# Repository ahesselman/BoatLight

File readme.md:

# Boat light controller

Controller for a boat light which indicates port and starboard. 

## Description

BoatLight is an LED ring system designed to indicate the port (red) and starboard (green) sides of a boat. It supports eight user-selectable modes, which can be toggled using a physical button. The currently selected mode is saved to persistent storage, so it resumes automatically after a power cycle.

The device is solar-powered. It monitors the voltage from a connected solar panel to determine whether it should be active or idle. When the solar panel voltage drops below 2.35V, the device activates. When the voltage rises above 2.40V, the device enters an idle state to conserve power.

## System overview

* **Power source**: solar panel and USB input
* **Battery**: ?
* **Charging module**: TP4056 for battery charging management
* **Microcontroller**: ATTiny85 for controlling the LEDs and handling user input
* **LEDs**: 16 SK6812 addressable RGBW LEDs
* **User input**: Single push-button for mode selection
* **Power control**: P-channel MOSFET to switch LED power

### Power management

1. Charging circuit

* **TP4056 module**: Connect the solar panel and USB input through appropriate diodes to the TP4056 module's input.
* **Battery connection**: The battery connects to the BAT+ and BAT- terminals of the TP4056.

2. Load sharing

To allow the system to operate while charging and prevent the battery from supplying power when external sources are available, load sharing is implemented

3. Voltage monitoring

A voltage divider is used to monitor the solar panel voltage. This allows the ATTiny85 to detect when the solar voltage drops below 2.35 and activate the LEDs accordingly. To improve stability and prevent unwanted rapid switching, hysterisis is applied. 

### Control circuit

1. ATTiny85 Microcontroller

* **Power supply**: powered from the battery through a voltage regeulator (if necessary).

* **Inputs**:
    * **Voltage divider**: Connected to an ADC pin to monitor solar voltage.
    * **Push-button**: Connected to a digital input pin with a pull-up resistor for mode selection.

* **Outputs**:
    * **LED Control**: A digital output pin connected to the data line of the SK6812 LED strip.
    * **MOSFET control**: A digital output pin to control  the gate of the P-channel MOSFET, switching the LED POWER.

2. P-Channel MOSFET

Used to switch the power for the SK6812 LEDs. The gate is controlled by the the ATTiny85, allowing the microcontroller to disconnect power from the LEDs when not in use, conserving battery life.

## Getting Started

### Dependencies

* Adafruit_NeoPixel

### Setup

* https://www.instructables.com/How-to-Program-an-Attiny85-From-an-Arduino-Uno/

## Authors
LedOptions

### Executing program

## Version History

* 0.1
    * Initial release

## Acknowledgments

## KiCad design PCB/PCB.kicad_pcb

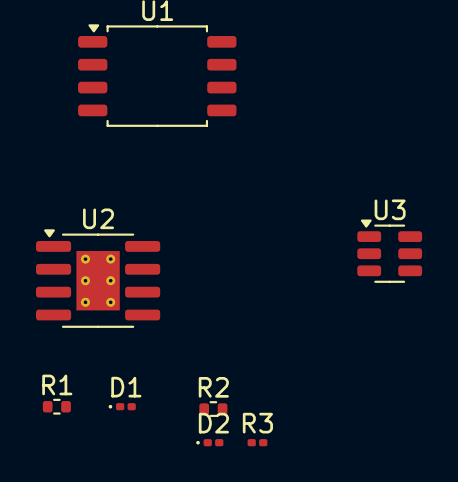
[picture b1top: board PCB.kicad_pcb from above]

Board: 2 copper layers, 8 parts (0 on the bottom side), 6 nets, no tracks yet.

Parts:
D1: Green; LED_0201_0603Metric
D2: Red; LED_0201_0603Metric
R1, R2: 1K; R_0402_1005Metric
R3: 1.2K; R_0201_0603Metric
U1: ATtiny85-20S; SOIC-8_5.3x5.3mm_P1.27mm
U2: TP4056-42-ESOP8; SOIC-8-1EP_3.9x4.9mm_P1.27mm_EP2.41x3.3mm_ThermalVias
U3: DW01A; SOT-23-6

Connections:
unnamed: D1.2 (A), D2.2 (A)
unnamed: D1.1 (K), R1.2
unnamed: D2.1 (K), R2.2
unnamed: R3.1, U2.2 (PROG)
unnamed: R2.1, U2.7 (~CHRG)
unnamed: R1.1, U2.6 (~STDBY)

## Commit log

2025-05-16 added readme
2025-05-16 added images of light modes
2025-05-16 Fix:laststeptime to global variable
2025-05-20 added various documentation
2025-05-20 refactored code to serveral messages various fixes due to testing added debug and wokwi switch
2025-05-20 updated documentation
2025-05-20 changes after review
2025-05-20 files moved
2025-05-21 added datasheets
2025-05-21 added led power switching added enum for light modes implemented save delay to EEPROM some minor code optimizations
2025-05-21 Update BoatLight.ino
    added comments
2025-05-21 Update BoatLight.ino
    updated comments
2025-05-22 updated button press function
2025-05-30 moved documents
2025-05-30 updated sketch
2025-05-30 sketch update
2025-06-02 fix: outputstate nt set
2025-06-02 chore: added support for long and sort button press chore: state is stored with a delay of 2 seconds fix: outputstate not set correctly fix: updated sketch, measure voltage before diode chore: added 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
2025-06-02 comments
2025-06-03 added pcb
2025-06-03 added tests
2025-06-03 updated voltage threshold only set voltage pin to high once do a sample read on the solar voltage updated sleep
2025-06-11 moved file
2025-06-11 refactor to seperate concerns
2025-06-11 added tesst for strip
2025-06-25 store lastsavedmode
2025-07-16 added mplab project for pic
2025-07-16 updated gitignore
2025-07-16 added test
2025-07-16 code improvements
2025-08-07 added support for variable number of leds
2025-08-07 renamed enum values for light mode
2025-08-07 removed unnecessary variable
2025-08-07 removed obsolete comments
2025-08-07 renamed variables
2025-09-04 added extra on-off button mode button only toggles modes changed pressed state to highvarious refactoring and name changes
2025-09-04 renames
2025-09-22 added comments
2025-09-22 updated threshold
2025-09-23 fix: off by 1 fix: last save mode fix: shut down procedure
2025-10-07 feat: improve mode handling and on/off behavior
    - Skip OFF_MODE when cycling through modes with the mode button
    - Update on/off button logic:
    - When ON → pressing turns LEDs off but remembers last active mode
    - When OFF → pressing restores the last active mode before power off
    - Improve EEPROM saving logic to prevent unnecessary writes immediately
    after turning back on
2025-11-10 - removed fading from sos - added flash mode - refactored mode count - added function declarations - refactored initialize button function to one implementation - added test at init for led strip - s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
2025-11-10 - moved init sos outside the function
2025-11-10 - fixed typo
2025-11-12 added images and documentation
2025-12-11 Measures Vcc via internal bandgap (1.1V)
2025-12-15 - fix: lowered upper threshold
2026-01-03 ran prettier
2026-01-03 added max brightness for white
2026-01-08 - ran prettier - added support for sos button - removed support for power pin
2026-01-08 - prevent floating of input button
2026-01-09 - added maxBrighnessWhite
2026-01-19 removed unnecessary line
2026-02-04 - cosmetic changes en renames - fixed:off by one - fixed: removed blocking code from extra modes handler
